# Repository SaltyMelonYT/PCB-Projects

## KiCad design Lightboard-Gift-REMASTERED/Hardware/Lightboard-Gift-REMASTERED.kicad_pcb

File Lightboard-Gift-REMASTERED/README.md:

## This is a revision of the original Lightboard PCB
This revision includes numerous changes to the PCB. Including:
* USB-C for power delivery (NOTE: This is not capable of data-transfer)
* Refined PCB design
* Larger mounting holes
* An actual power switch

## WANTED CHANGES
* Add JSON to keep the light mode, so when power is returned it is in the same mode as when it turned off

## HARDWARE NEEDED
* Ten (10) 1812 SMD resistors
* Ten (10) Common Cathode LEDs
* Four (4) 3m screws
* One (1) Raspberry Pi Pico
* One (1) 6mm x 6mm Switch (The kind found in Ardunio kits)
* One (1) PCB
* One (1) SPST Slide Switch (6.7x4.1mm W7.62mm P2.54mm)
* One (1) 6 pin USB-C Receptacle

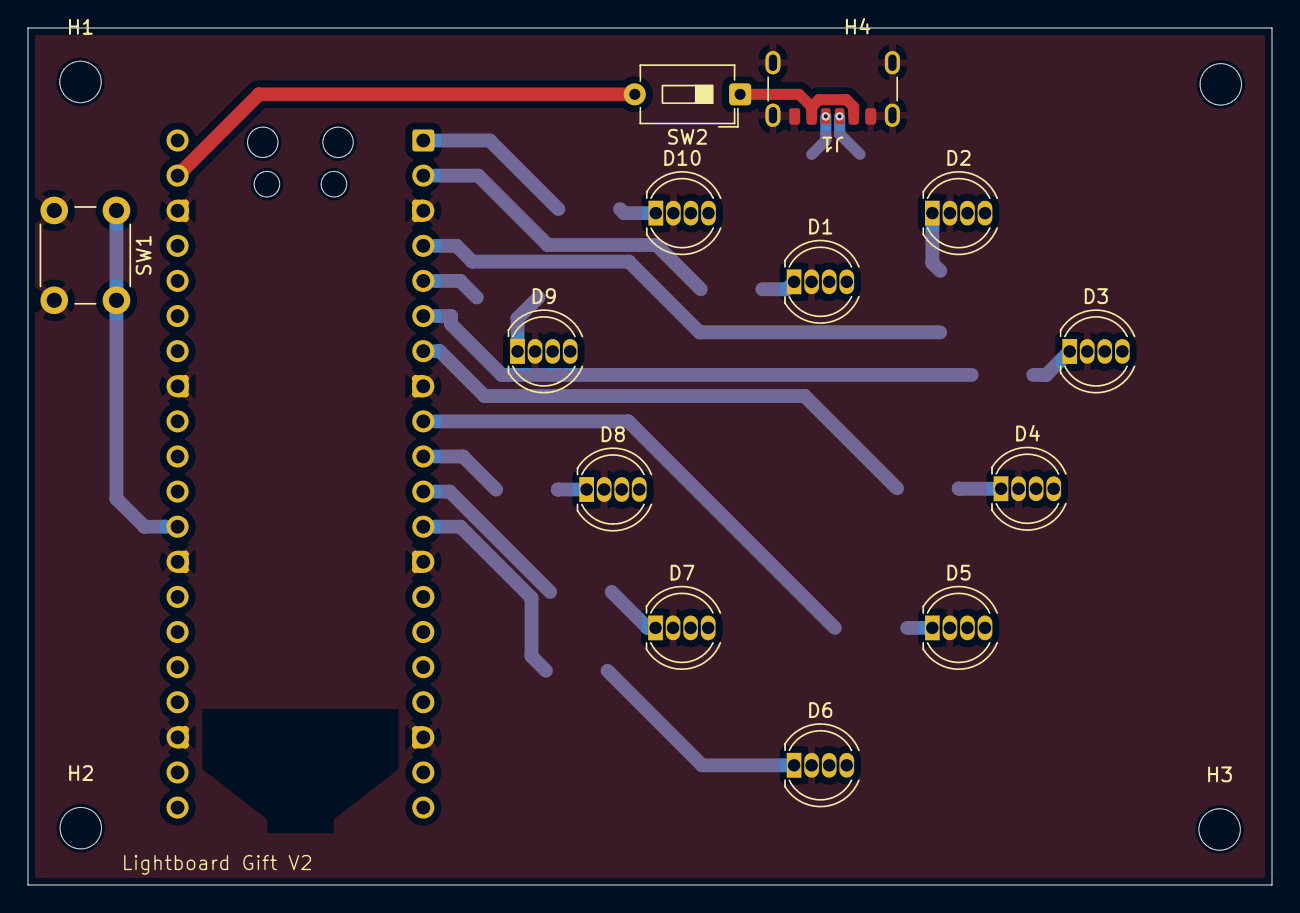
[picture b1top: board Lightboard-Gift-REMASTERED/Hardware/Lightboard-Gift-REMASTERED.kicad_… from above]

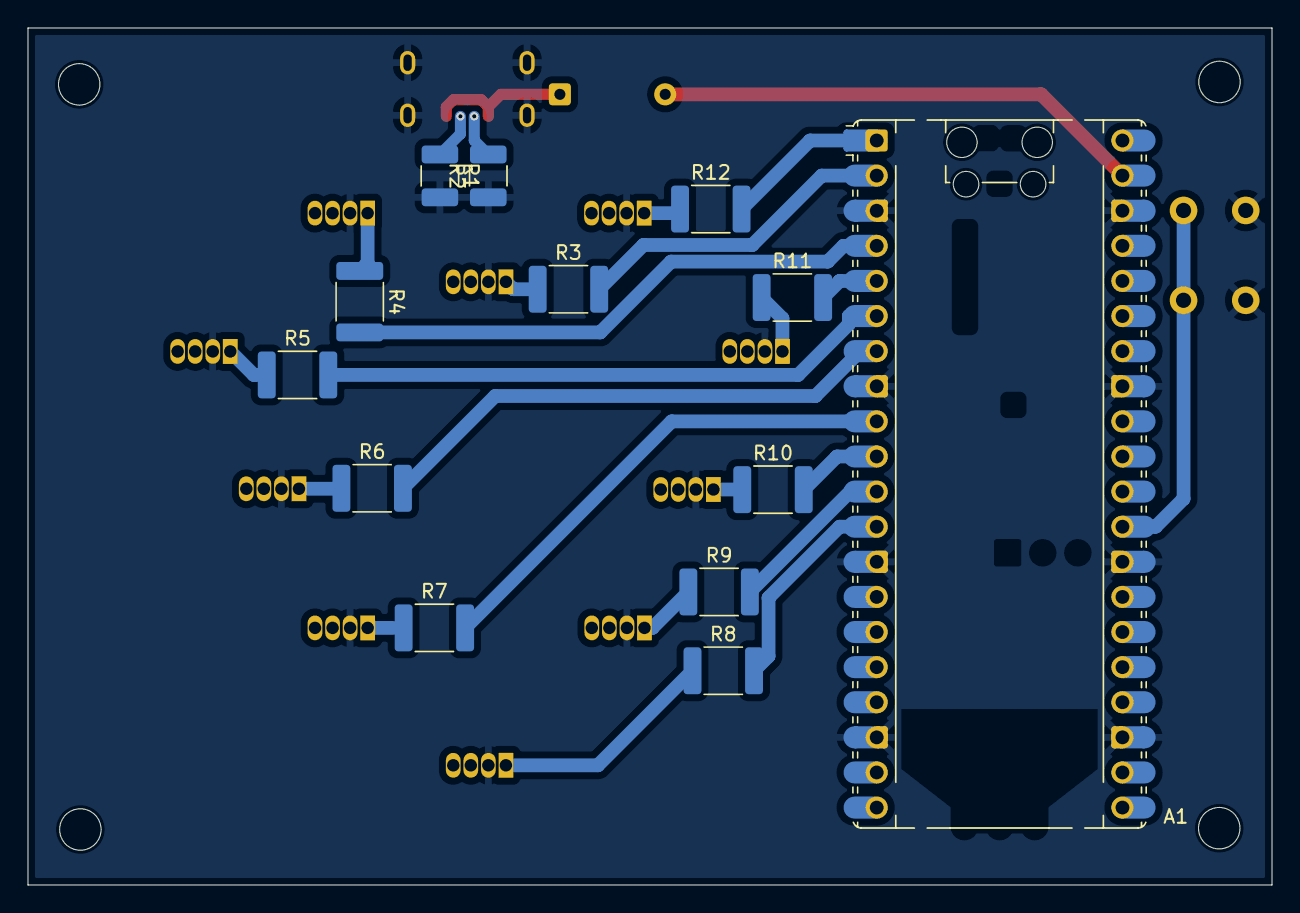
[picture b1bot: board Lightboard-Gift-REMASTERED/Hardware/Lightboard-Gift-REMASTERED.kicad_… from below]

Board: 2 copper layers, 90.0 x 62.0 mm, 30 parts (13 on the bottom side), 26 nets.

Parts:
A1: RaspberryPi_Pico; RaspberryPi_Pico_Common_Unspecified
D1, D2, D3, D4, D5, D6, D7, D8, D9, D10: LED_RKGB; LED_D5.0mm-4_RGB
H1, H2, H3, H4: MountingHole; MountingHole_3mm
J1: USB_C_Receptacle_PowerOnly_6P; USB_C_Receptacle_GCT_USB4125-xx-x_6P_TopMnt_Horizontal
R1, R2: 5k1; R_1210_3225Metric_Pad1.30x2.65mm_HandSolder
R3, R4, R5, R6, R7, R8, R9, R10, R11, R12: R_Small; R_1812_4532Metric_Pad1.30x3.40mm_HandSolder
SW1: SW_Push; SW_PUSH_6mm_H4.3mm
SW2: SW_SPST; SW_DIP_SPSTx01_Slide_6.7x4.1mm_W7.62mm_P2.54mm_LowProfile

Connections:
GND: A1.3 (GND), A1.8 (GND), A1.13 (GND), A1.18 (GND), A1.23 (GND), A1.28 (GND), A1.33 (AGND), A1.38 (GND), D1.2 (K), D2.2 (K), D3.2 (K), D4.2 (K), D5.2 (K), D6.2 (K), D7.2 (K), D8.2 (K), D9.2 (K), D10.2 (K), J1.A12 (GND), J1.B12 (GND), J1.S1 (SHIELD), R1.2, R2.1, SW1.2
unnamed: A1.29 (GPIO22), SW1.1
unnamed: D1.1 (RA), R3.1
unnamed: D2.1 (RA), R4.1
unnamed: D3.1 (RA), R5.1
unnamed: D4.1 (RA), R6.1
unnamed: D5.1 (RA), R7.1
unnamed: D6.1 (RA), R8.1
unnamed: D7.1 (RA), R9.1
unnamed: D8.1 (RA), R10.1
unnamed: D9.1 (RA), R11.1
unnamed: D10.1 (RA), R12.1
unnamed: J1.A5 (CC1), R1.1
unnamed: J1.B5 (CC2), R2.2
unnamed: J1.A9 (VBUS), J1.B9 (VBUS), SW2.1 (A)
RED0: A1.2 (GPIO1), R3.2
RED1: A1.4 (GPIO2), R4.2
RED2: A1.6 (GPIO4), R5.2
RED3: A1.7 (GPIO5), R6.2
RED4: A1.9 (GPIO6), R7.2
RED5: A1.12 (GPIO9), R8.2
RED6: A1.11 (GPIO8), R9.2
RED7: A1.10 (GPIO7), R10.2
RED8: A1.5 (GPIO3), R11.2
RED9: A1.1 (GPIO0), R12.2
VBUS: A1.39 (VSYS), SW2.2 (B)

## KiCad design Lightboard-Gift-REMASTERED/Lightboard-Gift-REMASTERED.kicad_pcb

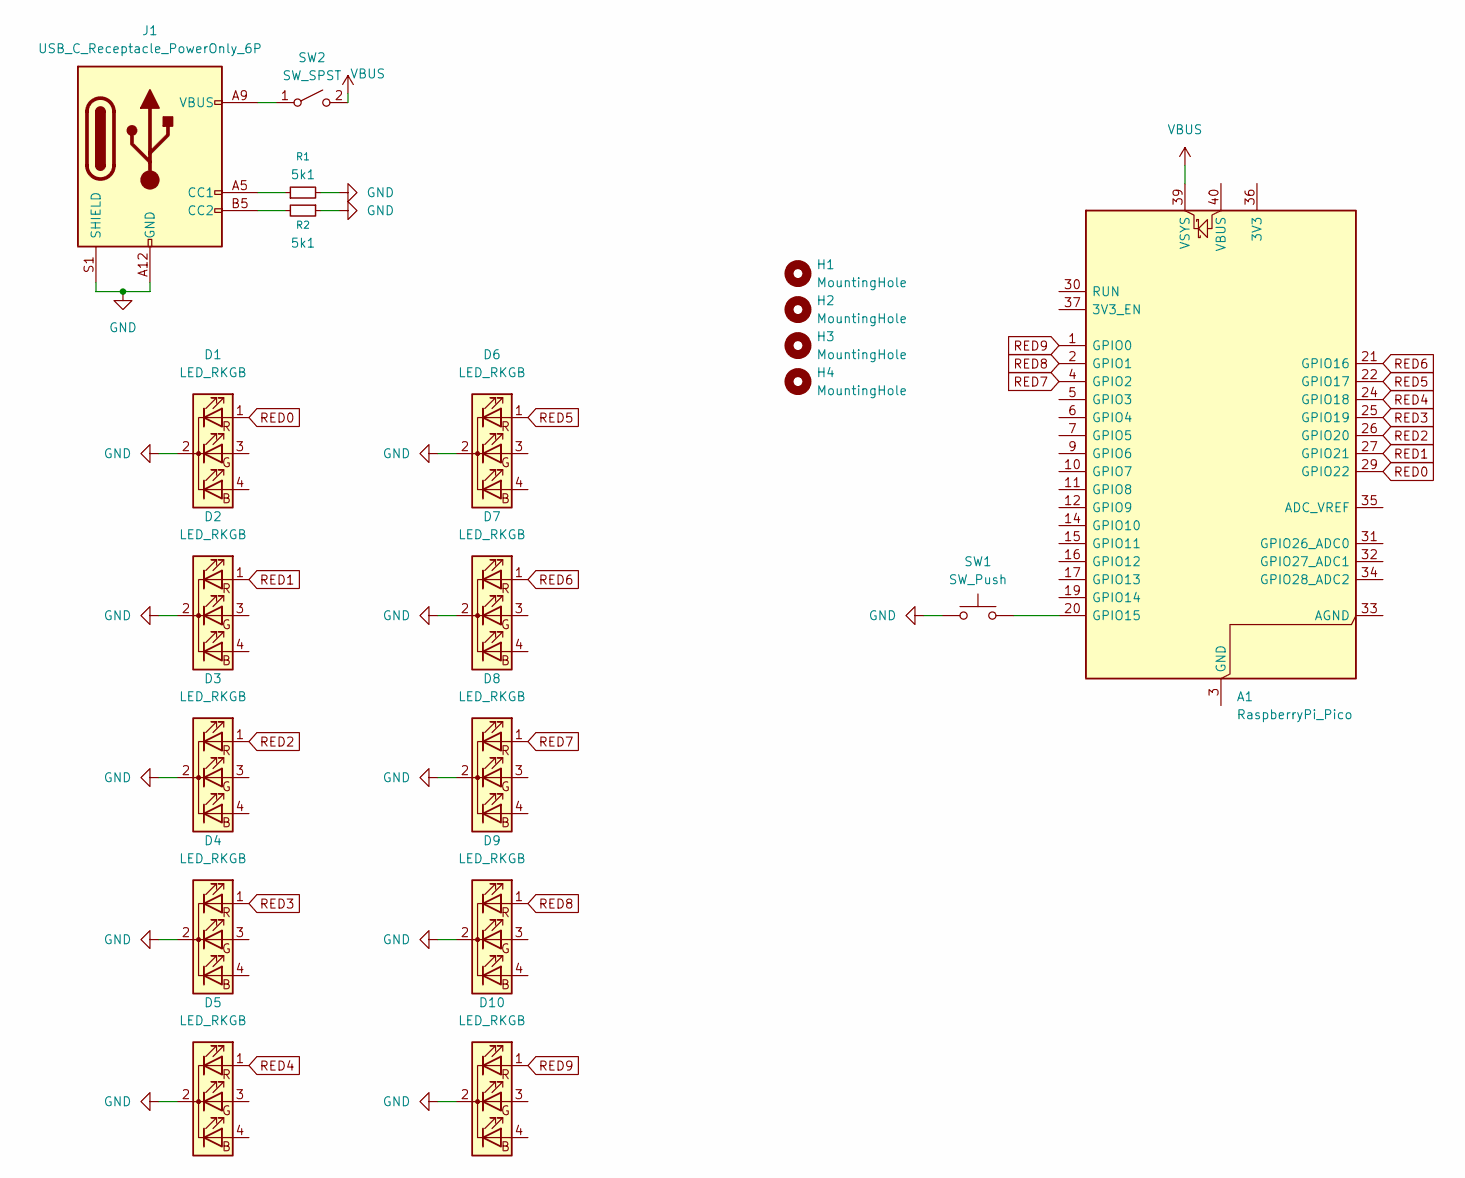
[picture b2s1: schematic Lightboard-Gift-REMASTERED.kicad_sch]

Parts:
A1: RaspberryPi_Pico; RaspberryPi_Pico_Common_Unspecified
D1, D2, D3, D4, D5, D6, D7, D8, D9, D10: LED_RKGB; LED_D5.0mm-4_RGB
H1, H2, H3, H4: MountingHole; MountingHole_3mm
J1: USB_C_Receptacle_PowerOnly_6P; USB_C_Receptacle_GCT_USB4125-xx-x_6P_TopMnt_Horizontal
R1, R2: 5k1; R_1210_3225Metric_Pad1.30x2.65mm_HandSolder
SW1: SW_Push; SW_PUSH_6mm_H4.3mm
SW2: SW_SPST; SW_DIP_SPSTx01_Slide_6.7x4.1mm_W7.62mm_P2.54mm_LowProfile

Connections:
GND: D1.2 (K), D2.2 (K), D3.2 (K), D4.2 (K), D5.2 (K), D6.2 (K), D7.2 (K), D8.2 (K), D9.2 (K), D10.2 (K), J1.A12 (GND), J1.B12 (GND), J1.S1 (SHIELD), R1.2, R2.1, SW1.1
unnamed: A1.3 (GND), A1.8 (GND), A1.13 (GND), A1.18 (GND), A1.23 (GND), A1.28 (GND), A1.38 (GND)
unnamed: A1.20 (GPIO15), SW1.2
unnamed: J1.A5 (CC1), R1.1
unnamed: J1.B5 (CC2), R2.2
unnamed: J1.A9 (VBUS), J1.B9 (VBUS), SW2.1 (A)
RED0: A1.29 (GPIO22), D1.1 (RA)
RED1: A1.27 (GPIO21), D2.1 (RA)
RED2: A1.26 (GPIO20), D3.1 (RA)
RED3: A1.25 (GPIO19), D4.1 (RA)
RED4: A1.24 (GPIO18), D5.1 (RA)
RED5: A1.22 (GPIO17), D6.1 (RA)
RED6: A1.21 (GPIO16), D7.1 (RA)
RED7: A1.4 (GPIO2), D8.1 (RA)
RED8: A1.2 (GPIO1), D9.1 (RA)
RED9: A1.1 (GPIO0), D10.1 (RA)
VBUS: A1.39 (VSYS), SW2.2 (B)

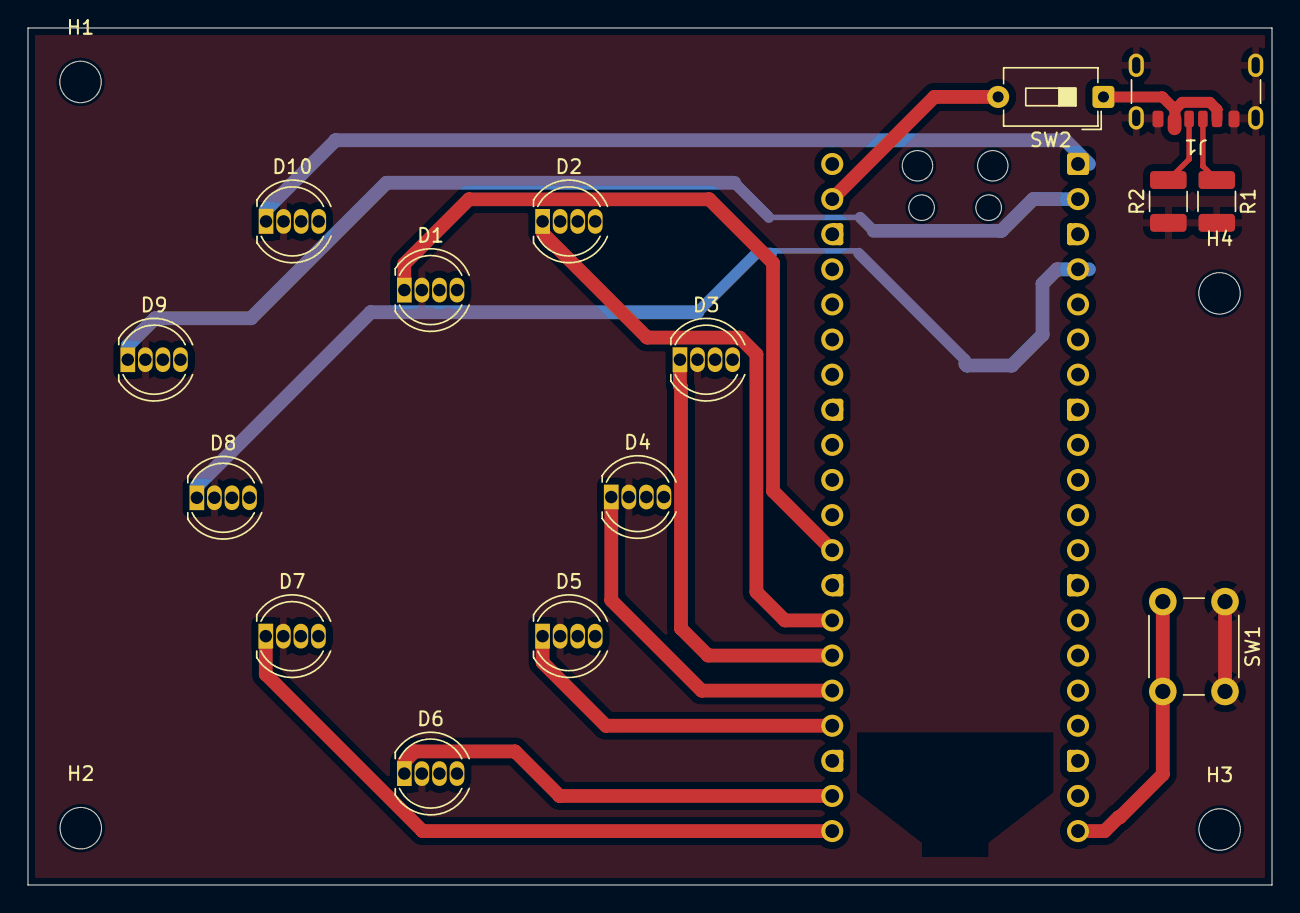
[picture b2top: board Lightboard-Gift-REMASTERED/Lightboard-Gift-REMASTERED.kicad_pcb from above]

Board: 2 copper layers, 90.0 x 62.0 mm, 20 parts (1 on the bottom side), 17 nets.

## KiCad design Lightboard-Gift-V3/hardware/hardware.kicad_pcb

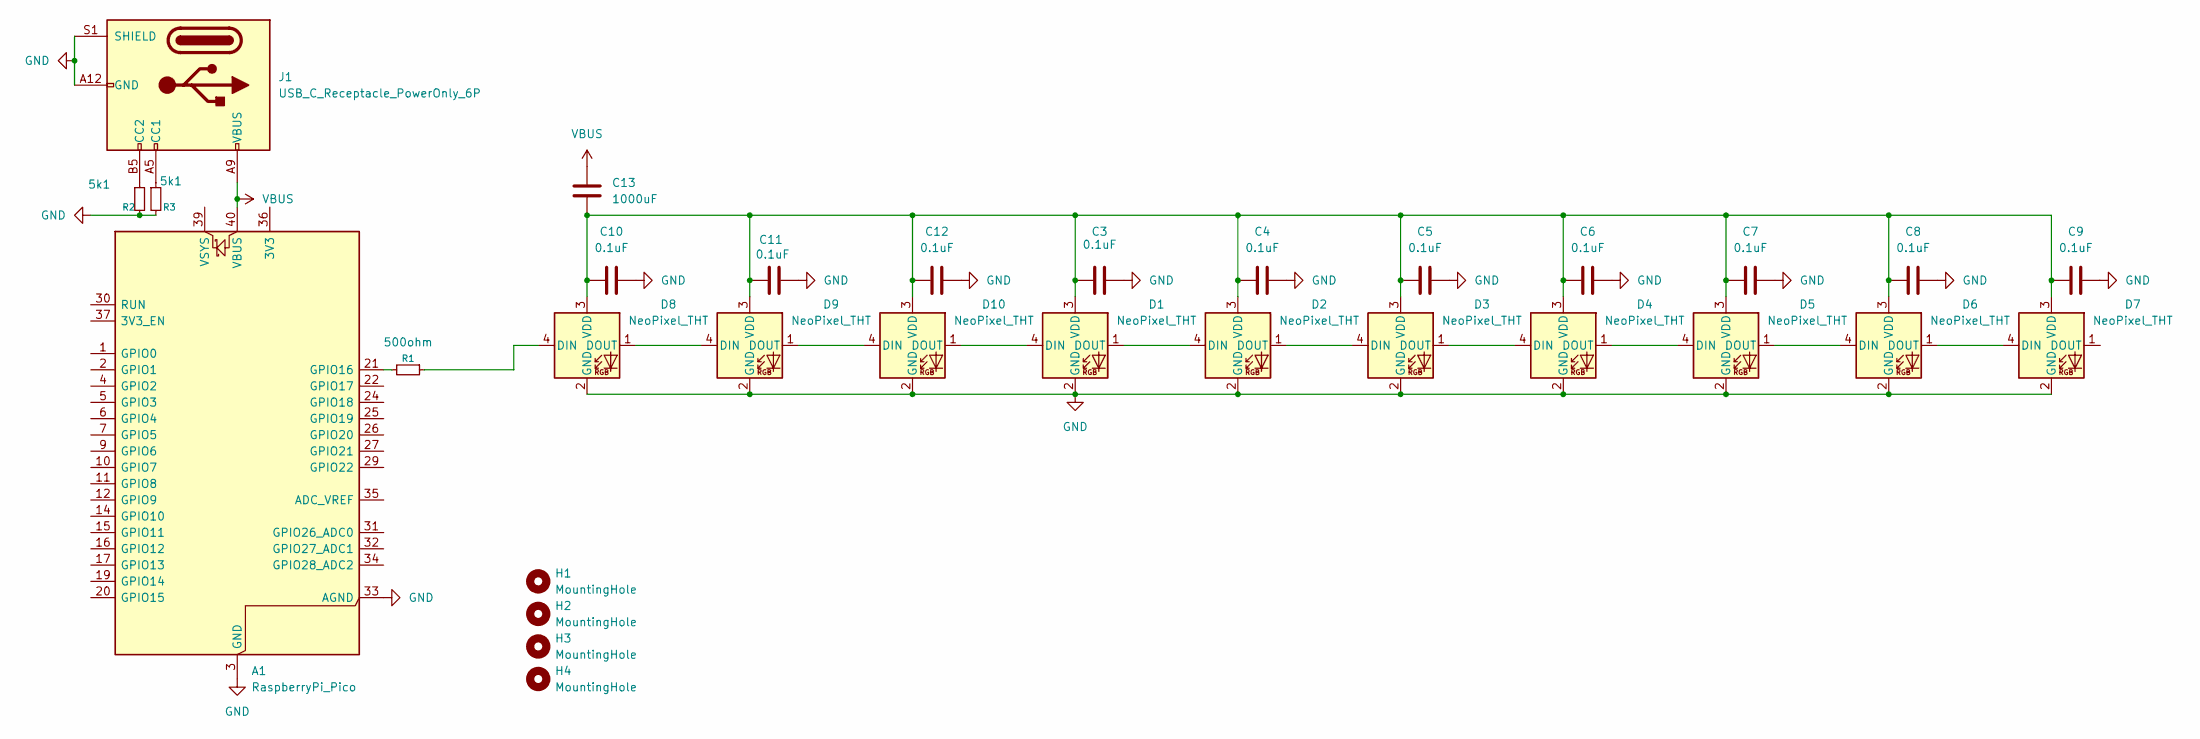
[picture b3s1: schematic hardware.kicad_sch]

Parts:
A1: RaspberryPi_Pico; RaspberryPi_Pico_Common_Unspecified
C3, C4, C5, C6, C7, C8, C9, C10, C11, C12: 0.1uF; C_1812_4532Metric_Pad1.57x3.40mm_HandSolder
C13: 1000uF; C_1812_4532Metric_Pad1.57x3.40mm_HandSolder
D1, D2, D3, D4, D5, D6, D7, D8, D9, D10: NeoPixel_THT; LED_D5.0mm-4_RGB
H1, H2, H3, H4: MountingHole; MountingHole_3.2mm_M3
J1: USB_C_Receptacle_PowerOnly_6P; USB_C_Receptacle_GCT_USB4125-xx-x-0190_6P_TopMnt_Horizontal
R1: 500ohm; R_0805_2012Metric_Pad1.20x1.40mm_HandSolder
R2, R3: 5k1; R_1812_4532Metric_Pad1.30x3.40mm_HandSolder

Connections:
GND: A1.3 (GND), A1.8 (GND), A1.13 (GND), A1.18 (GND), A1.23 (GND), A1.28 (GND), A1.33 (AGND), A1.38 (GND), C3.2, C4.2, C5.2, C6.2, C7.2, C8.2, C9.2, C10.2, C11.2, C12.2, D1.2 (GND), D2.2 (GND), D3.2 (GND), D4.2 (GND), D5.2 (GND), D6.2 (GND), D7.2 (GND), D8.2 (GND), D9.2 (GND), D10.2 (GND), J1.A12 (GND), J1.B12 (GND), J1.S1 (SHIELD), R2.2, R3.2
unnamed: A1.21 (GPIO16), R1.2
unnamed: D1.4 (DIN), D10.1 (DOUT)
unnamed: D1.1 (DOUT), D2.4 (DIN)
unnamed: C3.1, C4.1, C5.1, C6.1, C7.1, C8.1, C9.1, C10.1, C11.1, C12.1, C13.2, D1.3 (VDD), D2.3 (VDD), D3.3 (VDD), D4.3 (VDD), D5.3 (VDD), D6.3 (VDD), D7.3 (VDD), D8.3 (VDD), D9.3 (VDD), D10.3 (VDD)
unnamed: D2.1 (DOUT), D3.4 (DIN)
unnamed: D3.1 (DOUT), D4.4 (DIN)
unnamed: D4.1 (DOUT), D5.4 (DIN)
unnamed: D5.1 (DOUT), D6.4 (DIN)
unnamed: D6.1 (DOUT), D7.4 (DIN)
unnamed: D8.4 (DIN), R1.1
unnamed: D8.1 (DOUT), D9.4 (DIN)
unnamed: D9.1 (DOUT), D10.4 (DIN)
unnamed: J1.A5 (CC1), R3.1
unnamed: J1.B5 (CC2), R2.1
VBUS: A1.40 (VBUS), C13.1, J1.A9 (VBUS), J1.B9 (VBUS)

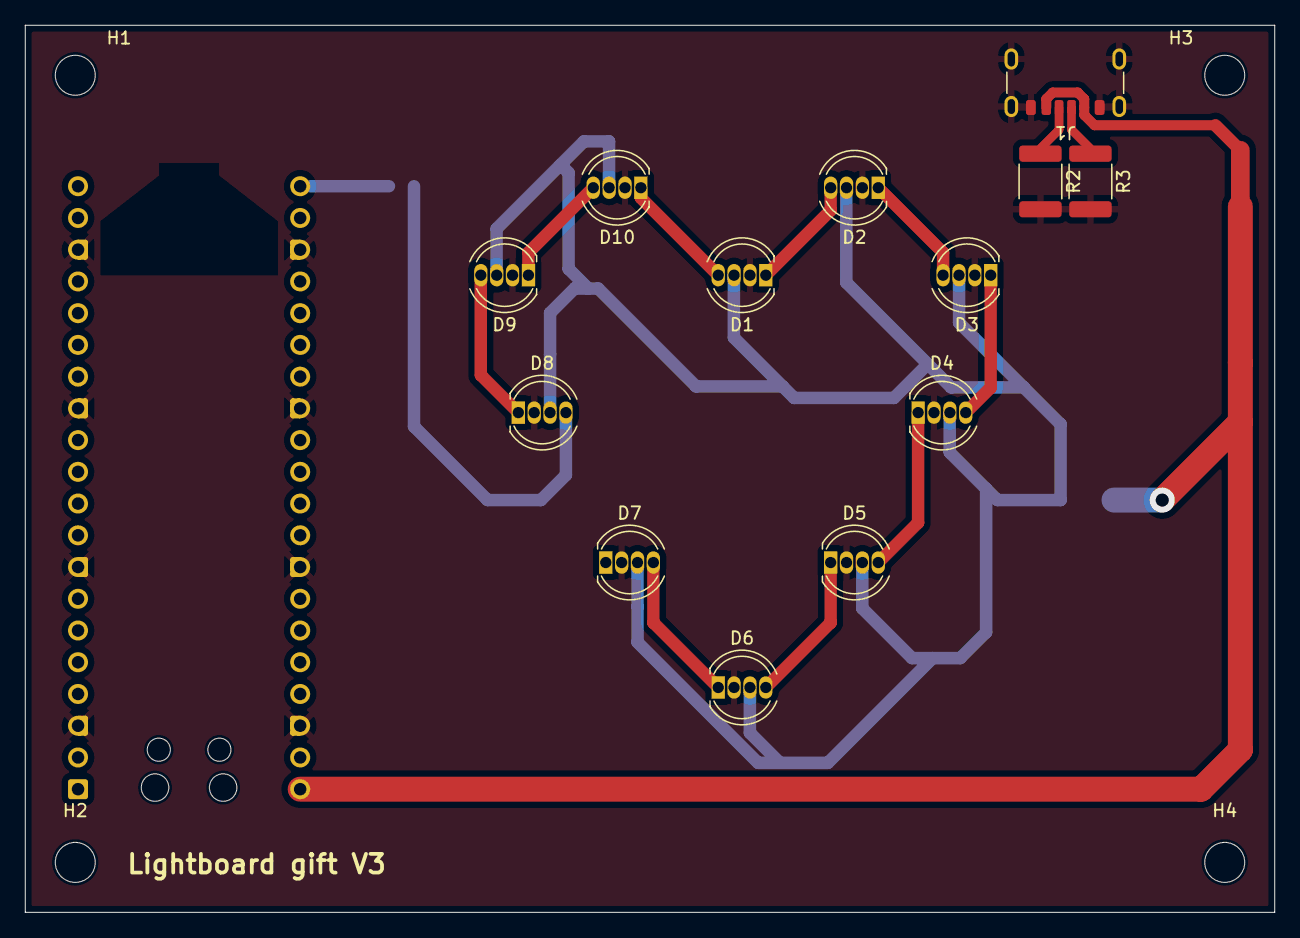
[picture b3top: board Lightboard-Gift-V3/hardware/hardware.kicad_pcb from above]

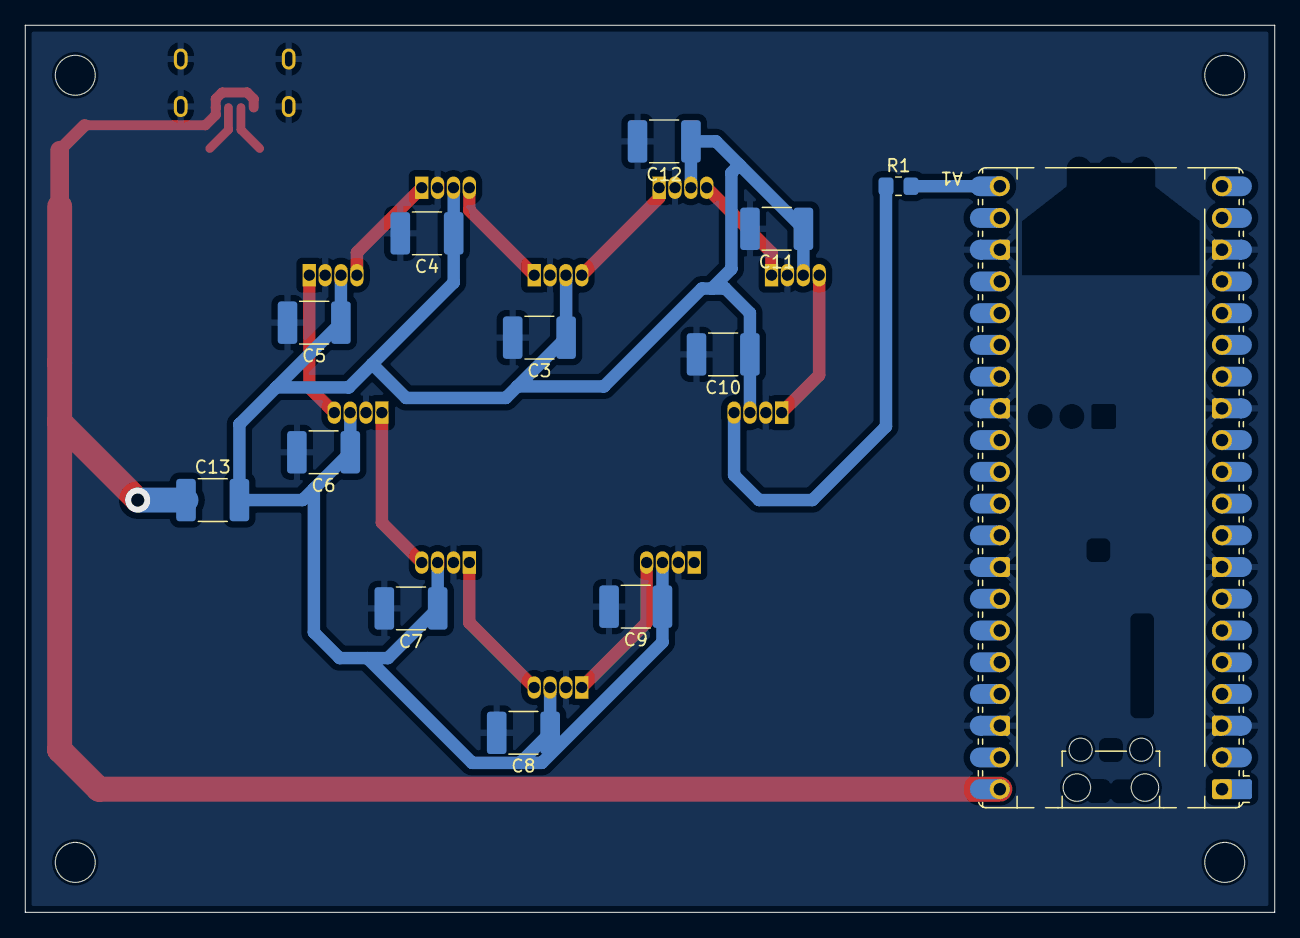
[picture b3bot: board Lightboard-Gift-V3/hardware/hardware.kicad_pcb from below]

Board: 2 copper layers, 100.0 x 71.0 mm, 30 parts (13 on the bottom side), 16 nets.

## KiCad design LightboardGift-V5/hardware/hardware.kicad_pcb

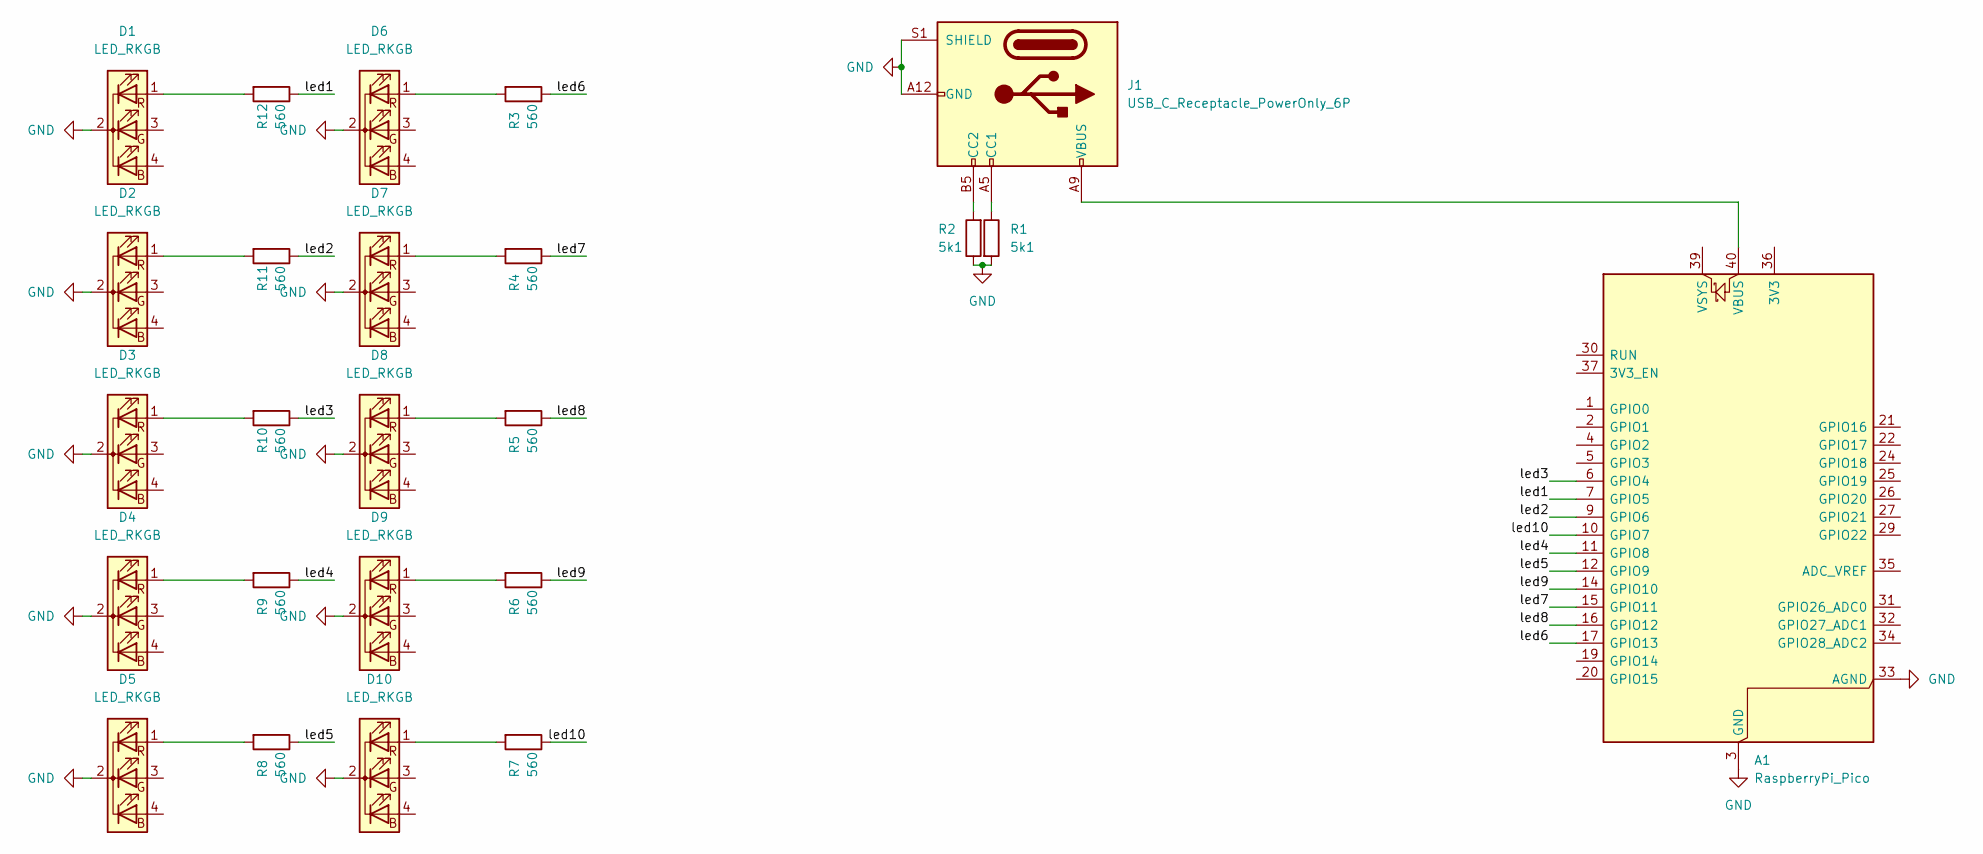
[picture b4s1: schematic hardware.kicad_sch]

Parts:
A1: RaspberryPi_Pico; RaspberryPi_Pico_Common_Unspecified
D1, D2, D3, D4, D5, D6, D7, D8, D9, D10: LED_RKGB; LED_D5.0mm-4_RGB
J1: USB_C_Receptacle_PowerOnly_6P; USB_C_Receptacle_GCT_USB4125-xx-x_6P_TopMnt_Horizontal
R1, R2: 5k1; R_1206_3216Metric_Pad1.30x1.75mm_HandSolder
R3, R4, R5, R6, R7, R8, R9, R10, R11, R12: 560; R_1206_3216Metric_Pad1.30x1.75mm_HandSolder

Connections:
/led1: A1.7 (GPIO5), R12.1
/led2: A1.9 (GPIO6), R11.1
/led3: A1.6 (GPIO4), R10.1
/led4: A1.11 (GPIO8), R9.1
/led5: A1.12 (GPIO9), R8.1
/led6: A1.17 (GPIO13), R3.1
/led7: A1.15 (GPIO11), R4.1
/led8: A1.16 (GPIO12), R5.1
/led9: A1.14 (GPIO10), R6.1
/led10: A1.10 (GPIO7), R7.1
GND: A1.3 (GND), A1.8 (GND), A1.13 (GND), A1.18 (GND), A1.23 (GND), A1.28 (GND), A1.33 (AGND), A1.38 (GND), D1.2 (K), D2.2 (K), D3.2 (K), D4.2 (K), D5.2 (K), D6.2 (K), D7.2 (K), D8.2 (K), D9.2 (K), D10.2 (K), J1.A12 (GND), J1.B12 (GND), J1.S1 (SHIELD), R1.2, R2.1
unnamed: A1.40 (VBUS), J1.A9 (VBUS), J1.B9 (VBUS)
unnamed: D1.1 (RA), R12.2
unnamed: D2.1 (RA), R11.2
unnamed: D3.1 (RA), R10.2
unnamed: D4.1 (RA), R9.2
unnamed: D5.1 (RA), R8.2
unnamed: D6.1 (RA), R3.2
unnamed: D7.1 (RA), R4.2
unnamed: D8.1 (RA), R5.2
unnamed: D9.1 (RA), R6.2
unnamed: D10.1 (RA), R7.2
unnamed: J1.A5 (CC1), R1.1
unnamed: J1.B5 (CC2), R2.2

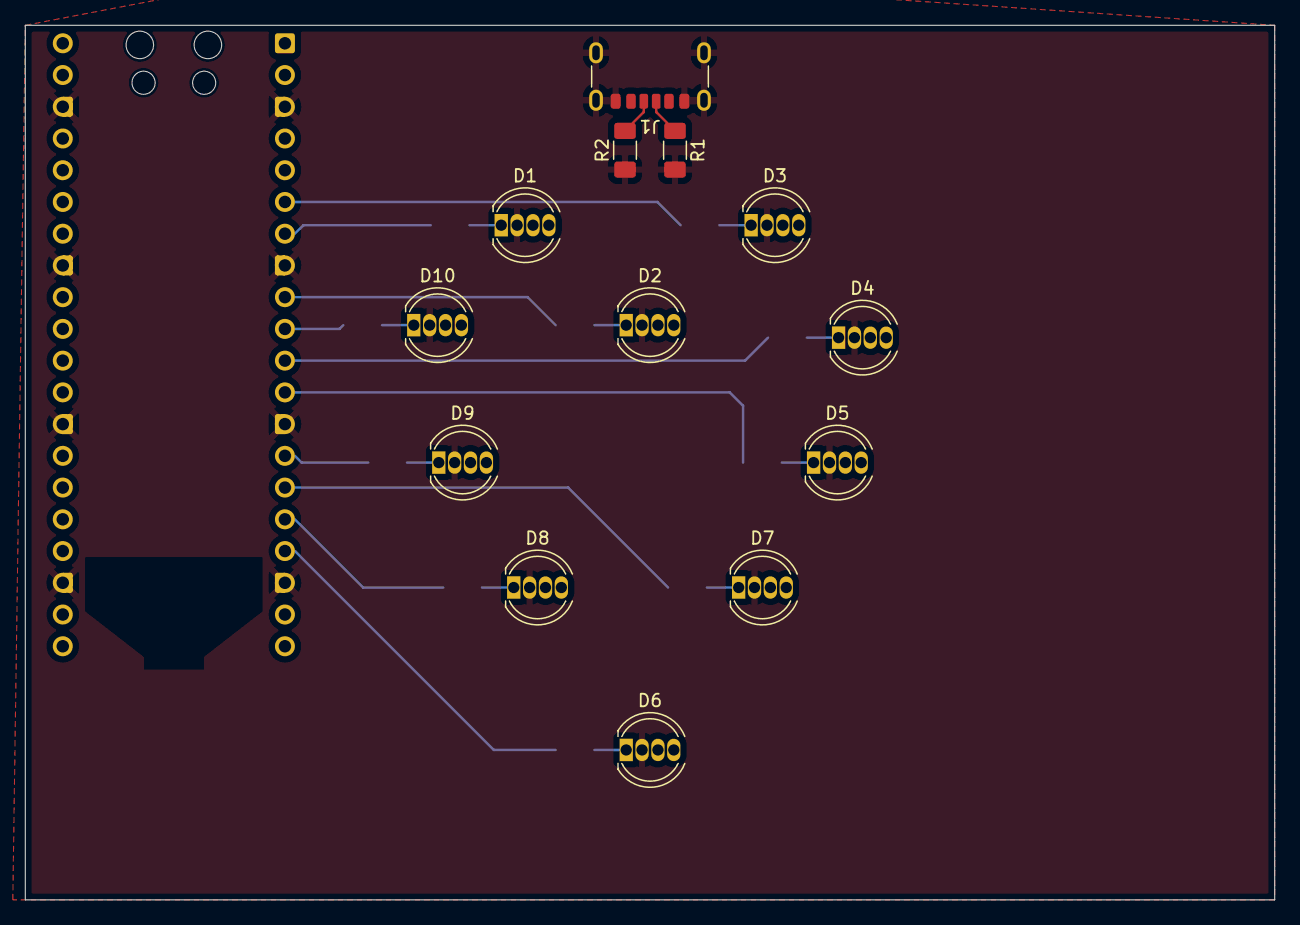
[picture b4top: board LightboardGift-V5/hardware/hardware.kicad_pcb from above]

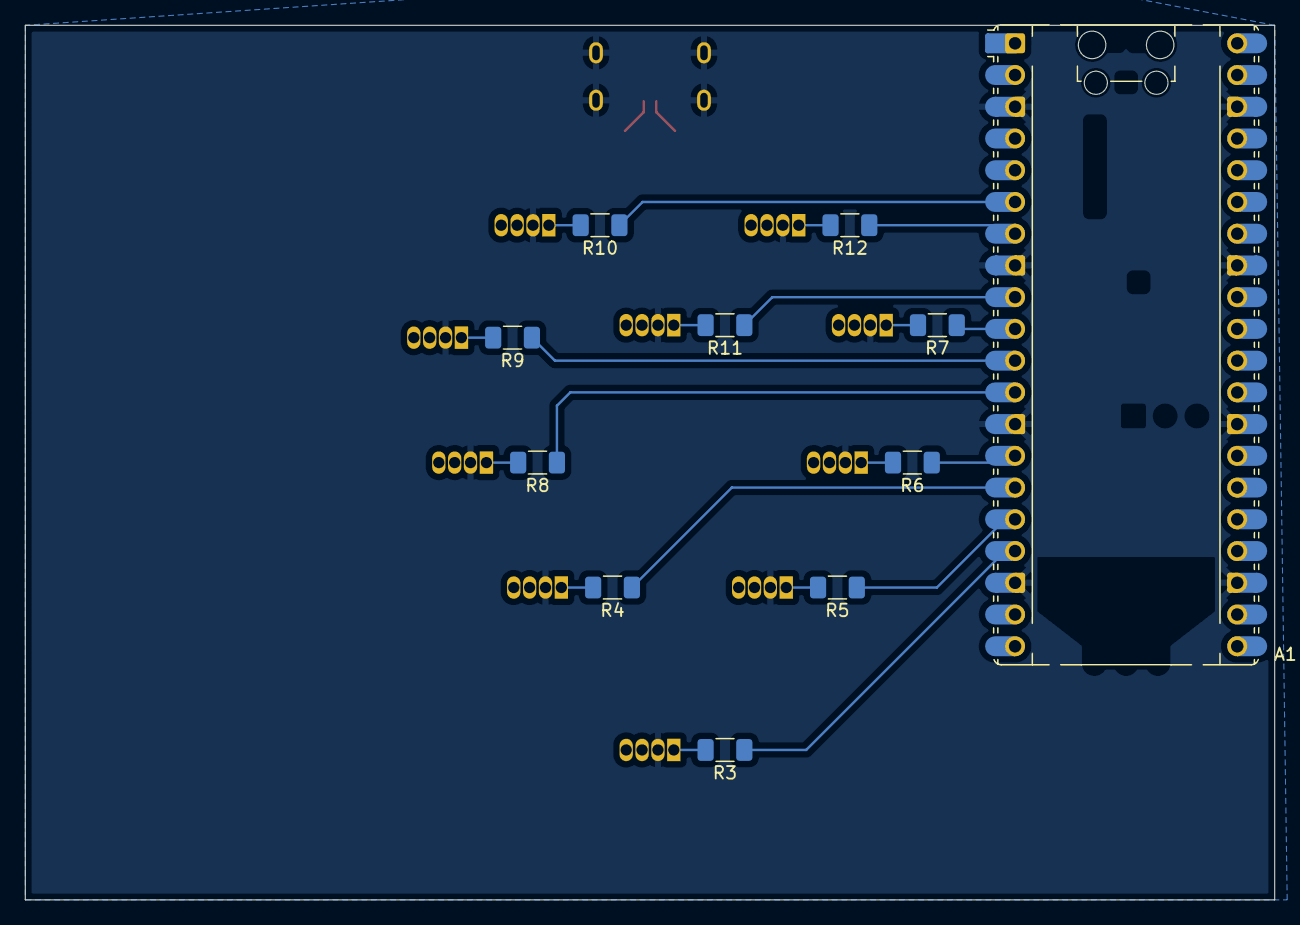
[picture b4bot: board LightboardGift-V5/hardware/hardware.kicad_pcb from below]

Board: 2 copper layers, 100.0 x 70.0 mm, 24 parts (11 on the bottom side), 24 nets.

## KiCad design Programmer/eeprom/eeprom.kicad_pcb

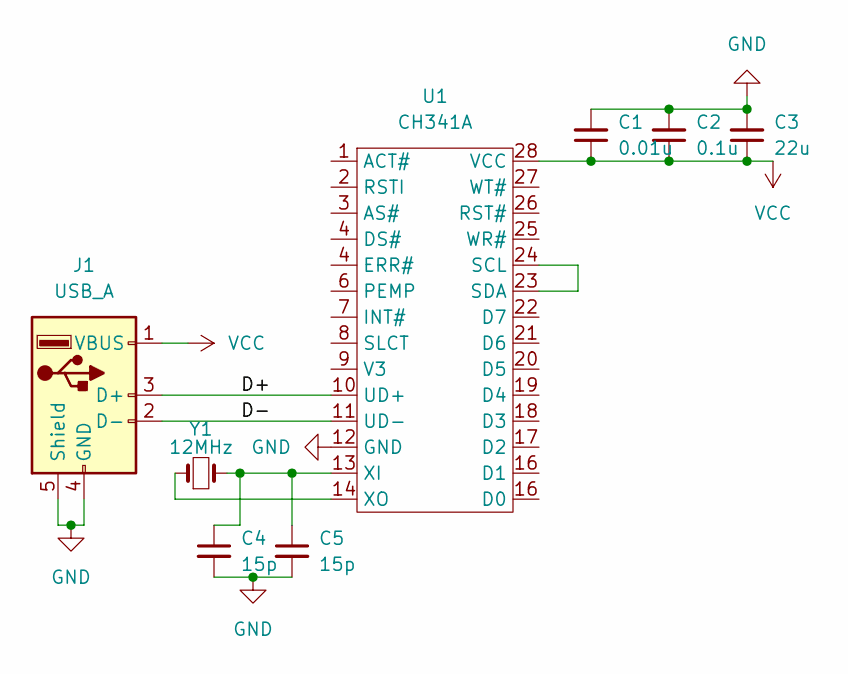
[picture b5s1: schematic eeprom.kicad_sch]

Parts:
C1: 0.01u; C_0504_1310Metric_Pad0.83x1.28mm_HandSolder
C2: 0.1u; C_0504_1310Metric_Pad0.83x1.28mm_HandSolder
C3: 22u; C_0504_1310Metric_Pad0.83x1.28mm_HandSolder
C4, C5: 15p; C_0504_1310Metric_Pad0.83x1.28mm_HandSolder
J1: USB_A; USB_A_CNCTech_1001-011-01101_Horizontal
U1: CH341A; SOP-28_8.4x18.16mm_P1.27mm
Y1: 12MHz; Crystal_SMD_5032-2Pin_5.0x3.2mm_HandSoldering

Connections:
/D+: J1.3 (D+), U1.10 (UD+)
/D-: J1.2 (D-), U1.11 (UD-)
GND: C1.2, C2.2, C3.2, C4.2, C5.2, J1.4 (GND), J1.5 (Shield), U1.12 (GND)
unnamed: U1.23 (SDA), U1.24 (SCL)
unnamed: C4.1, C5.1, U1.13 (XI), Y1.2
unnamed: U1.14 (XO), Y1.1
VCC: C1.1, C2.1, C3.1, J1.1 (VBUS), U1.28 (VCC)

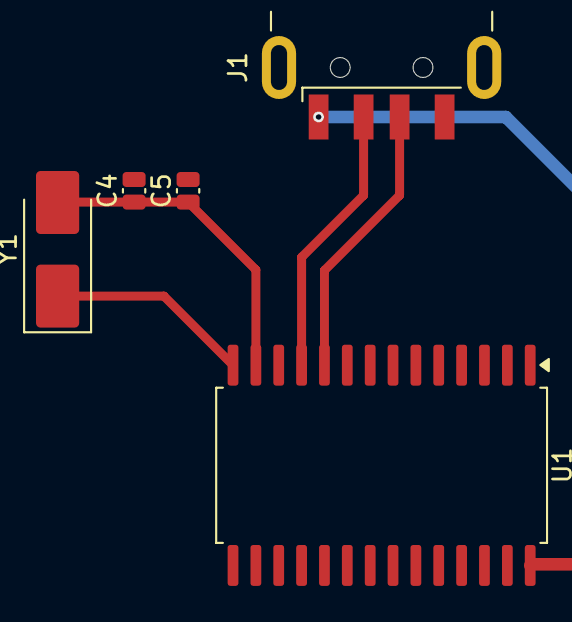
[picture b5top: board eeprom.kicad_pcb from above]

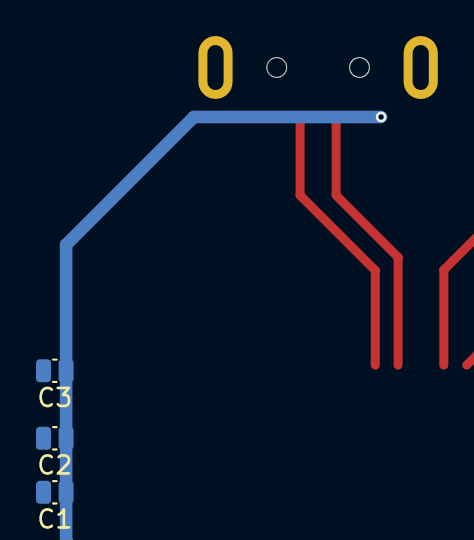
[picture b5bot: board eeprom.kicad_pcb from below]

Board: 2 copper layers, 8 parts (3 on the bottom side), 7 nets.
